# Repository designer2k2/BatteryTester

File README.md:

# BatteryTester
Arduino Shield to test 1-3S LiPo´s

There are KiCad Files (for 4.0.2) and the Arduino Programm here!

This shield has large resistors switched by mosfets, that gives the possibilty to change the load to the connected cells.

it measures the capacity and Internal resistance, you can plot the data in graphs if you like:

It is based on my prototype from here: http://www.designer2k2.at/mods/arduino/70-battery-tester

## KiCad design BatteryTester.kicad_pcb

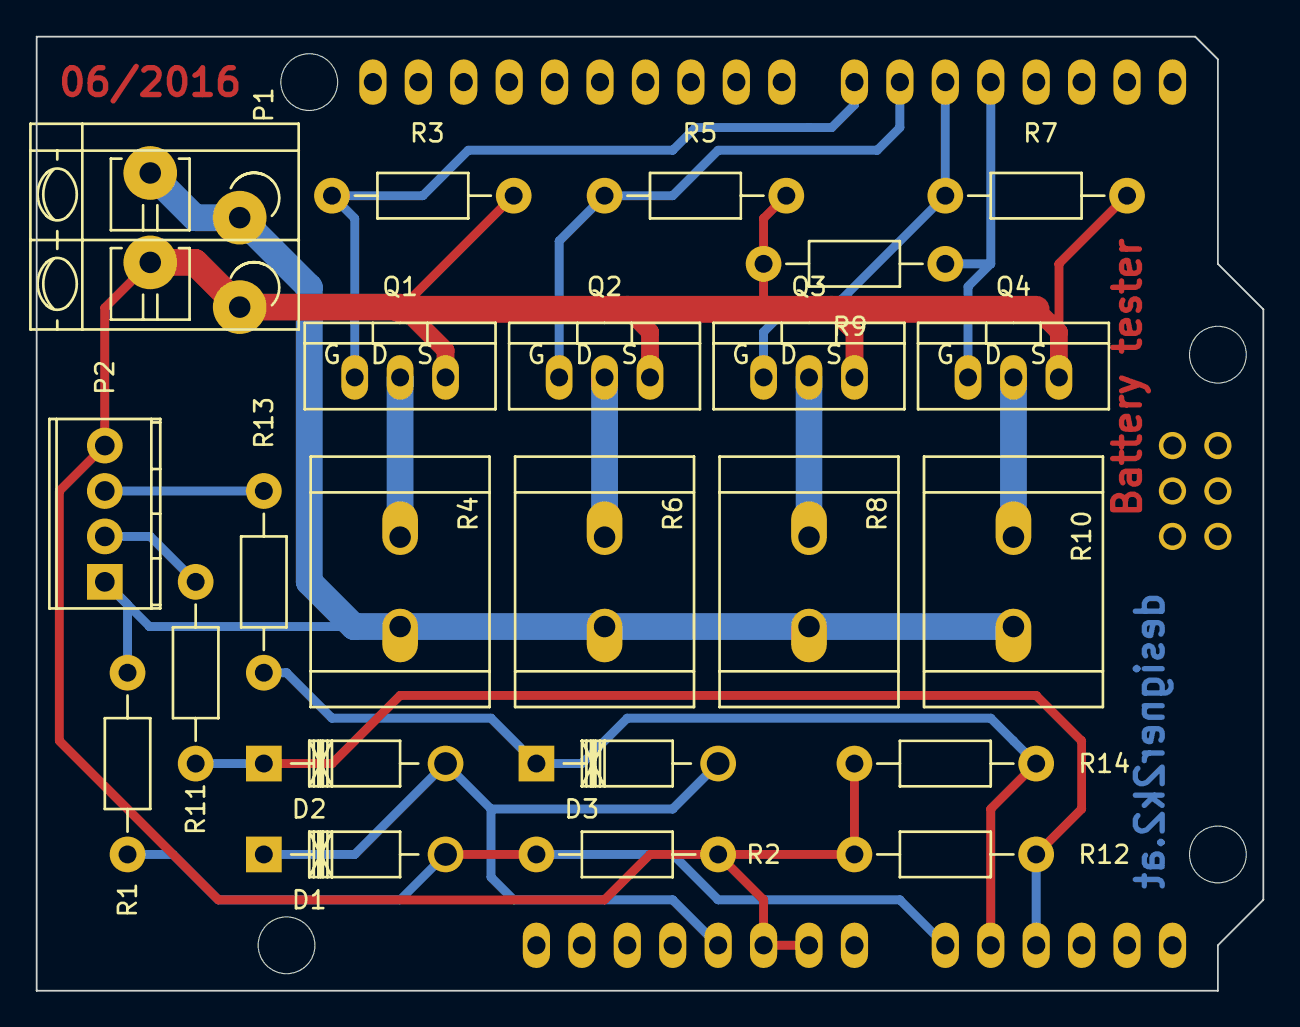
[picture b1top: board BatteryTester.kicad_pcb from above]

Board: 2 copper layers, 68.6 x 53.3 mm, 24 parts (0 on the bottom side), 16 nets.

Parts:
D1, D2, D3: DIODE; Diode_DO-41_SOD81_Horizontal_RM10
P1: CONN_01X02; TerminalBlock_WAGO-804_RM5mm_2pol
P2: CONN_01X04; TerminalBlock_Pheonix_MPT-2.54mm_4pol
Q1, Q2, Q3, Q4: MOSFET_N; TO-220_FET-GDS_Vertical
R1, R11, R12, R13, R14: 10k; Resistor_Horizontal_RM10mm
R2: 5k; Resistor_Horizontal_RM10mm
R3, R5, R7, R9: 100k; Resistor_Horizontal_RM10mm
R4, R6, R8, R10: 3.9; Resistor_Cement_Vertical_LargePads_KOA-BGR-5N-7N
SHIELD1: ARDUINO_SHIELD

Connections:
+5V: D1.2, D2.2, D3.2, SHIELD1.5V
GND: P1.2, P2.4, Q1.S, Q2.S, Q3.S, Q4.S, R2.2, R3.2, R5.2, R7.2, R9.2, R12.2, R14.2, SHIELD1.GND1, SHIELD1.GND2
unnamed: D1.1, R1.2, R2.1, SHIELD1.AD0
unnamed: D2.1, R11.2, R12.1, SHIELD1.AD2
unnamed: D3.1, R13.2, R14.1, SHIELD1.AD1
unnamed: P1.1, P2.1, R1.1, R4.1, R6.1, R8.1, R10.1
unnamed: P2.2, R11.1
unnamed: P2.3, R13.1
unnamed: Q1.D, R4.2
unnamed: Q1.G, R3.1, SHIELD1.7
unnamed: Q2.D, R6.2
unnamed: Q2.G, R5.1, SHIELD1.6
unnamed: Q3.D, R8.2
unnamed: Q3.G, R7.1, SHIELD1.5
unnamed: Q4.D, R10.2
unnamed: Q4.G, R9.1, SHIELD1.4

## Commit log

2016-06-01 Initial Fill
    KiCad 4.0.2 Files incl. Gerber´s that qualify for OSHpark
2016-06-01 Initial Fill
    Arduino Sourcecode (testet on Prototype, not on the PCB!)
2022-10-03 Arduino formatting
    [STRG]+[T] formatting
2022-10-04 Update to KiCad 6
2022-10-04 Add bom list
2022-10-08 Update Gerbers
2022-11-16 Create BatteryTester_schematic.pdf
    Add schematic
